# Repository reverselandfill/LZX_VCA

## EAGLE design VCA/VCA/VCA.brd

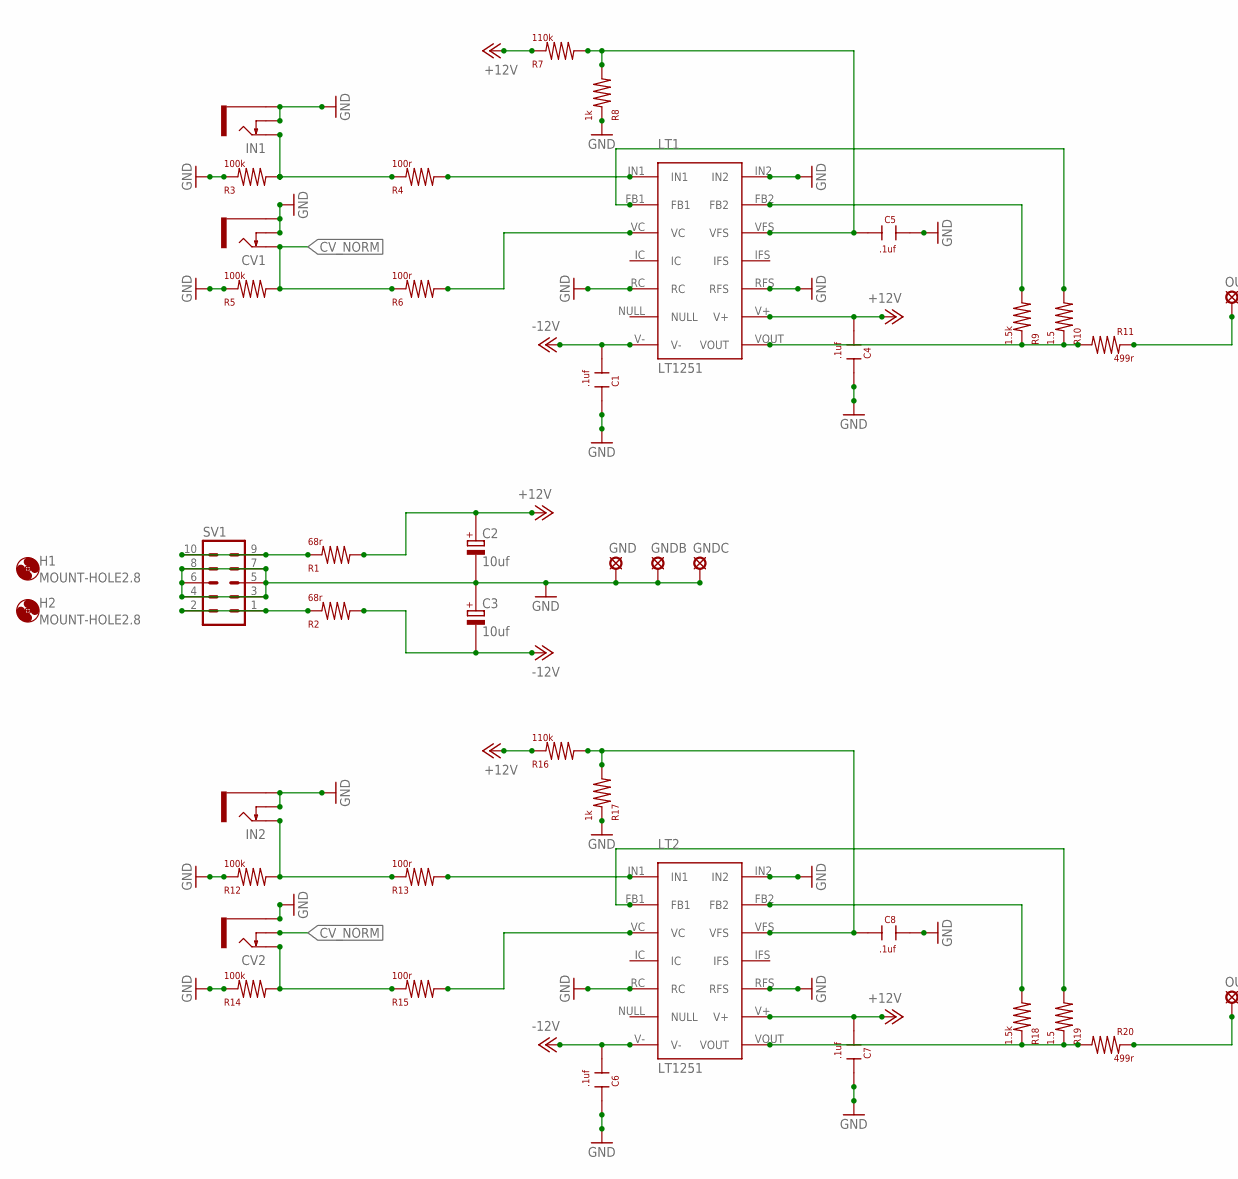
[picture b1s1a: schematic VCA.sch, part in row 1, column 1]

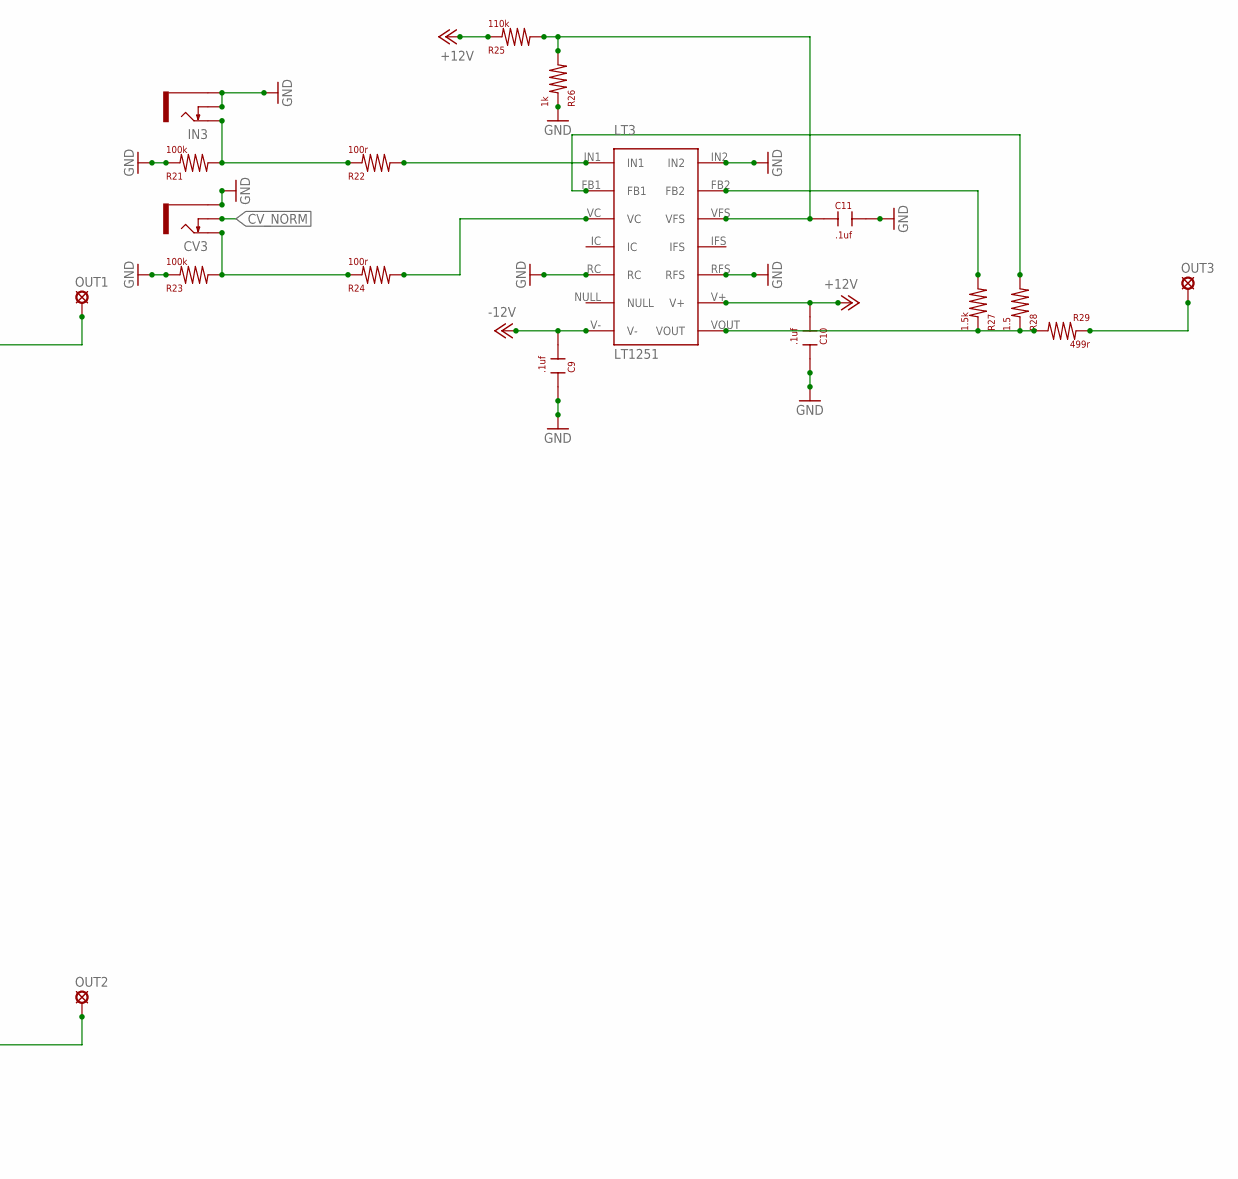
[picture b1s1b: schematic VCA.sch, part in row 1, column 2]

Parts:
C1, C4, C5, C6, C7, C8, C9, C10, C11: .1uf; CAPACITOR_FILM
C2, C3: 10uf; CAPACITOR_ELECTRO
CV1, CV2, CV3: PJ302M
GND: LSP10
GNDB: LSP10
GNDC: LSP10
H1, H2: MOUNT-HOLE2.8; 2,8
IN1, IN2, IN3: PJ302M
LT1, LT2, LT3: LT1251; TL1251
OUT1, OUT2, OUT3: LSP10
R1, R2: 68r; RESISTOR
R3, R5, R12, R14, R21, R23: 100k; RESISTOR
R4, R6, R13, R15, R22, R24: 100r; RESISTOR
R7, R16, R25: 110k; RESISTOR
R8, R17, R26: 1k; RESISTOR
R9, R18, R27: 1.5k; RESISTOR
R10, R19, R28: 1.5; RESISTOR
R11, R20, R29: 499r; RESISTOR
SV1: EURORACK10

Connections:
+12V: C2.+, C4.P$2, C7.P$2, C10.P$2, LT1.V+, LT2.V+, LT3.V+, R1.P$2, R7.P$1, R16.P$1, R25.P$1
-12V: C1.P$2, C3.-, C6.P$2, C9.P$2, LT1.V-, LT2.V-, LT3.V-, R2.P$2
CV_NORM: CV1.TIP, CV2.SW (SWITCH), CV3.SW (SWITCH), R5.P$2, R6.P$1
GND: C1.P$1, C2.-, C3.+, C4.P$1, C5.P$1, C6.P$1, C7.P$1, C8.P$1, C9.P$1, C10.P$1, C11.P$1, CV1.GND (SLEEVE), CV1.SW (SWITCH), CV2.GND (SLEEVE), CV3.GND (SLEEVE), GND.MP, GNDB.MP, GNDC.MP, IN1.GND (SLEEVE), IN1.SW (SWITCH), IN2.GND (SLEEVE), IN2.SW (SWITCH), IN3.GND (SLEEVE), IN3.SW (SWITCH), LT1.IN2, LT1.RC, LT1.RFS, LT2.IN2, LT2.RC, LT2.RFS, LT3.IN2, LT3.RC, LT3.RFS, R3.P$1, R5.P$1, R8.P$1, R12.P$1, R14.P$1, R17.P$1, R21.P$1, R23.P$1, R26.P$1, SV1.3, SV1.4, SV1.5, SV1.6, SV1.7, SV1.8
unnamed: LT1.IN1, R4.P$2
unnamed: R1.P$1, SV1.9, SV1.10
unnamed: IN2.TIP, R12.P$2, R13.P$1
unnamed: LT1.VC, R6.P$2
unnamed: CV2.TIP, R14.P$2, R15.P$1
unnamed: LT2.IN1, R13.P$2
unnamed: C5.P$2, LT1.VFS, R7.P$2, R8.P$2
unnamed: R2.P$1, SV1.1, SV1.2
unnamed: IN1.TIP, R3.P$2, R4.P$1
unnamed: LT1.VOUT, R9.P$1, R10.P$1, R11.P$2
unnamed: LT1.FB2, R9.P$2
unnamed: LT1.FB1, R10.P$2
unnamed: OUT1.MP, R11.P$1
unnamed: LT2.VC, R15.P$2
unnamed: C8.P$2, LT2.VFS, R16.P$2, R17.P$2
unnamed: LT2.VOUT, R18.P$1, R19.P$1, R20.P$2
unnamed: LT2.FB2, R18.P$2
unnamed: LT2.FB1, R19.P$2
unnamed: OUT2.MP, R20.P$1
unnamed: IN3.TIP, R21.P$2, R22.P$1
unnamed: LT3.IN1, R22.P$2
unnamed: LT3.VC, R24.P$2
unnamed: C11.P$2, LT3.VFS, R25.P$2, R26.P$2
unnamed: LT3.VOUT, R27.P$1, R28.P$1, R29.P$2
unnamed: LT3.FB2, R27.P$2
unnamed: LT3.FB1, R28.P$2
unnamed: OUT3.MP, R29.P$1
unnamed: CV3.TIP, R23.P$2, R24.P$1

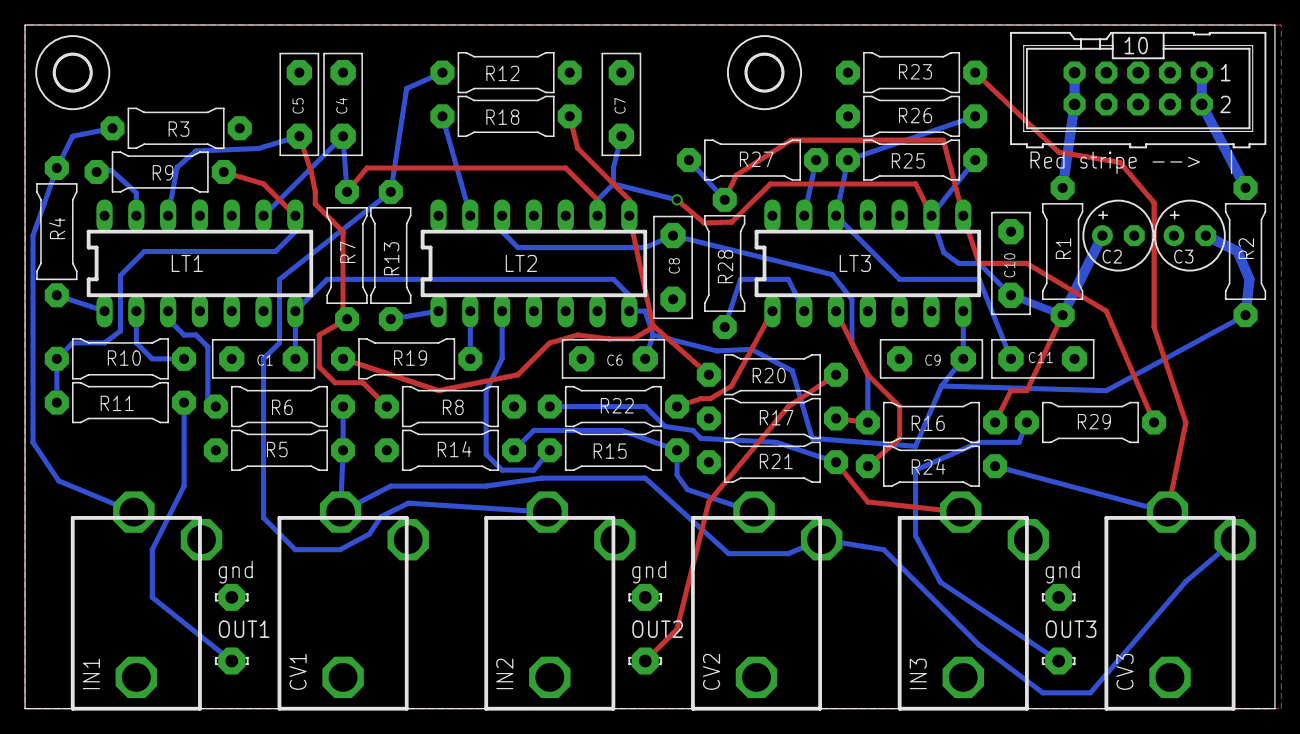
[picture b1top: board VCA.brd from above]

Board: 2 copper layers, 99.8 x 54.6 mm, 58 parts (0 on the bottom side), 32 nets.

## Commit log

2017-05-17 test
    testing
